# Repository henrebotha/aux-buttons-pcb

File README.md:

# Fightstick aux buttons PCB

This is a design for a small PCB containing three tactile pushbutton switches. It's intended for use as menu buttons in a fightstick, but can be used for any number of things. A 4-pin JST-PH connector can be used to connect this to other circuits. It occupies a footprint of about 8×50 mm on the control panel, but the physical size is 10×60 mm (more like 10×70 mm if you account for connecting something to the JST).

The buttons and connections are labeled on the bottom side of the PCB. The buttons are connected to a common ground, marked `G` next to the appropriate pin on the JST.

The PCB is designed to mount under the control panel on a pair of 6 mm spacers (it has two 3.2 mm holes that can accept an M3 thread). The switches are roughly 9 mm tall, so mounting the PCB this way will allow the switches to protrude from the top of a control panel that is less than 3 mm thick. The mounting holes and switches are all in one line. The distance between the mounting holes and switches is 9 mm, and the distance between switches is 12 mm (all these dimensions are centre to centre). The switches need a hole with a diameter of at least 4.5 mm. See the diagram below for recommended panel cutouts.

The design assumes the use of Omron B3F-1070 switches, but any pushbutton in the common 6×6 mm footprint should work, assuming it's tall enough. (The JST-PH connector sits on the same side of the PCB as the switches, which is why spacers & tall buttons are necessary.)

This project was designed using EasyEDA.

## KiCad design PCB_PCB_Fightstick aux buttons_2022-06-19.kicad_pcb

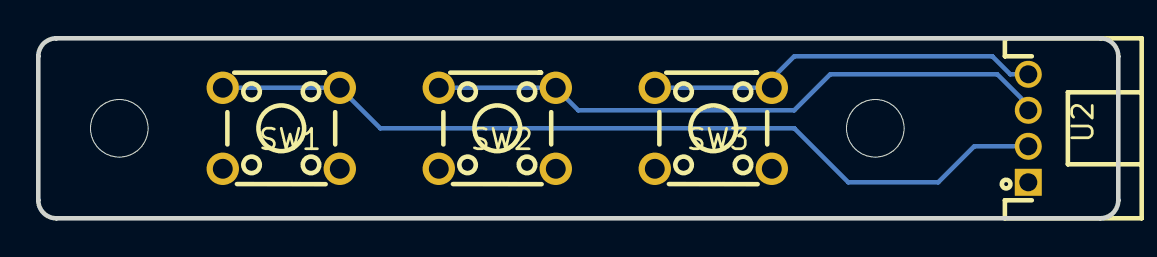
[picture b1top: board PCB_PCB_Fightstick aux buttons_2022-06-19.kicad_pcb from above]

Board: 2 copper layers, 60.0 x 10.0 mm, 4 parts (0 on the bottom side), 4 nets.

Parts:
SW1, SW2, SW3: B3F-1070; SW-TH_4P-L6.2-W6.2-P4.50-LS6.5
U2: S4B-PH-K-S-(LF)(SN); CONN-TH_4P-P2.00_S4B-PH-K-S-LF-SN

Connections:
GND: SW1.3, SW1.4, SW2.3, SW2.4, SW3.3, SW3.4, U2.1
SW1_2: SW1.1, SW1.2, U2.2
SW2_2: SW2.1, SW2.2, U2.3
SW3_2: SW3.1, SW3.2, U2.4

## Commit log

2022-07-05 Initial commit
    Imported from EasyEDA.
2022-07-06 Add README
